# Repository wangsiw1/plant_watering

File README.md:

# Plant watering

A simple 1 main to multiple workers hardware setup to monitor soil moisture and water series of plant pots automatically.

Main device:
- Gateway of the setup, managing the workers, hosting web server for user interactions
- Monitoring water level from water container with capacitive sensor
- Controlling pump for watering

Worker device:
- Monitoring 1 or more soil moisture sensors and reporting to main
- Controlling 1 or more two-position three-way solenoid valves to redirect water to different plant pots

> **Disclaimer**: LLM has been used in this project as part of the learning process. On hardware side, Google Gemini, Claude AI, and OpenAI ChatGPT were used to explain usage of components, knowledge cross check, and parts recommendation. On software side, GitHub Copilot agent in Visual Studio Code was used to generate part of the code based on design document. Human review, revise, and test was conducted every round of generation.

## Design

- MCU:
    Considering the price and wireless requirement, ESP32 C3 was chosen.

- Power: 
    - Since main device will do the heavy duties(Always on, WiFi connection and web server host, pump driving, etc.), a 12V DC input using common DC barrel plug adapter was used to provide continuous power. 
    - Amount of workers can be scaled up and locations varies based on the plant location, while worker can be less power hungry, rechargeable LiPo battery is used.

- Communication:
    - Bluetooth between main and worker for sensor reading reporting and watering command sending. 
    - For easy scalability and setup process, all devices use BLE broadcast to send messages and filter message by MAC address of sendor, no connection is required.

- Function:
    - Users add workers to main by Bluetooth MAC address. Main will probe added workers and learn details upon first status report(worker having 1/8/16 ports available)
    - Users set watering duration, soil moisture threshold, and automatic watering interval for each plant pot, plus the system-wide active time range and data-sync interval.
    - After enabling auto watering, main collects sensor readings, starts pump and commands workers to trigger solenoid valve, then let workers go to deep sleep mode during time interval to save power.
    - Solenoid valve will be triggered one by one, meaning only one pot will be watered at a single time, due to battery current and pump power limitation.

## Hardware

### V1

For the initial idea, because of the nature of similarity between main and worker(1 sensor, 1 peripheral), it was decided to use a single PCB design for both devices with compatibility added to fit different parts on the same board. 

Since a 12V pump was used, a 12V solenoid valve was also chosen. Then all differences are as follow:
- Different sockets for pump(screw terminal) and valve(GH 1.25 socket), lined up next to each other on the PCB, use one of them as needed.
- Different sensor pin numbers(3 pins for soil moisture and 4 pins for water level), since both are XH 2.54, and both have pin 3 as data output, put a single 4 pin footprint, and use different parts.
- Different VIN and GND pin sequences for sensors, use two 0 ohm with solder pads in 2*2 grid to bridge trace to achieve different sequences on different orientations.

Being first version of the project and first personal hardware project, this one has severe design flaws due to lacking of knowledge, hardware understanding, and product reasearch. It was scrapped later.

#### Shared Schematic & PCB

#### Main

#### Worker

### V2

Design of main device is basically V1, but with dimension changed to fit case and worker compatibility removed, as worker is fully redesigned.

For worker, after reviewing the total cost of V1 worker, it was really expensive for users owning dozens of pots of plant. In V2, worker had numbers of monitored plant expand from 1 to 8, and can be expanded to 16 in the future.

To reduce cost and weight, power was cut from 12V to 5V. Battery was moved from large lithium battery pack to flat LiPo with charging & 5V boost converter module. Solenoid valve was also changed to a different 5V version.

There are still several minor issues with this version, not function breaking, but are documented in the schematic and shall be fixed in the next revision.

#### Main

#### Worker

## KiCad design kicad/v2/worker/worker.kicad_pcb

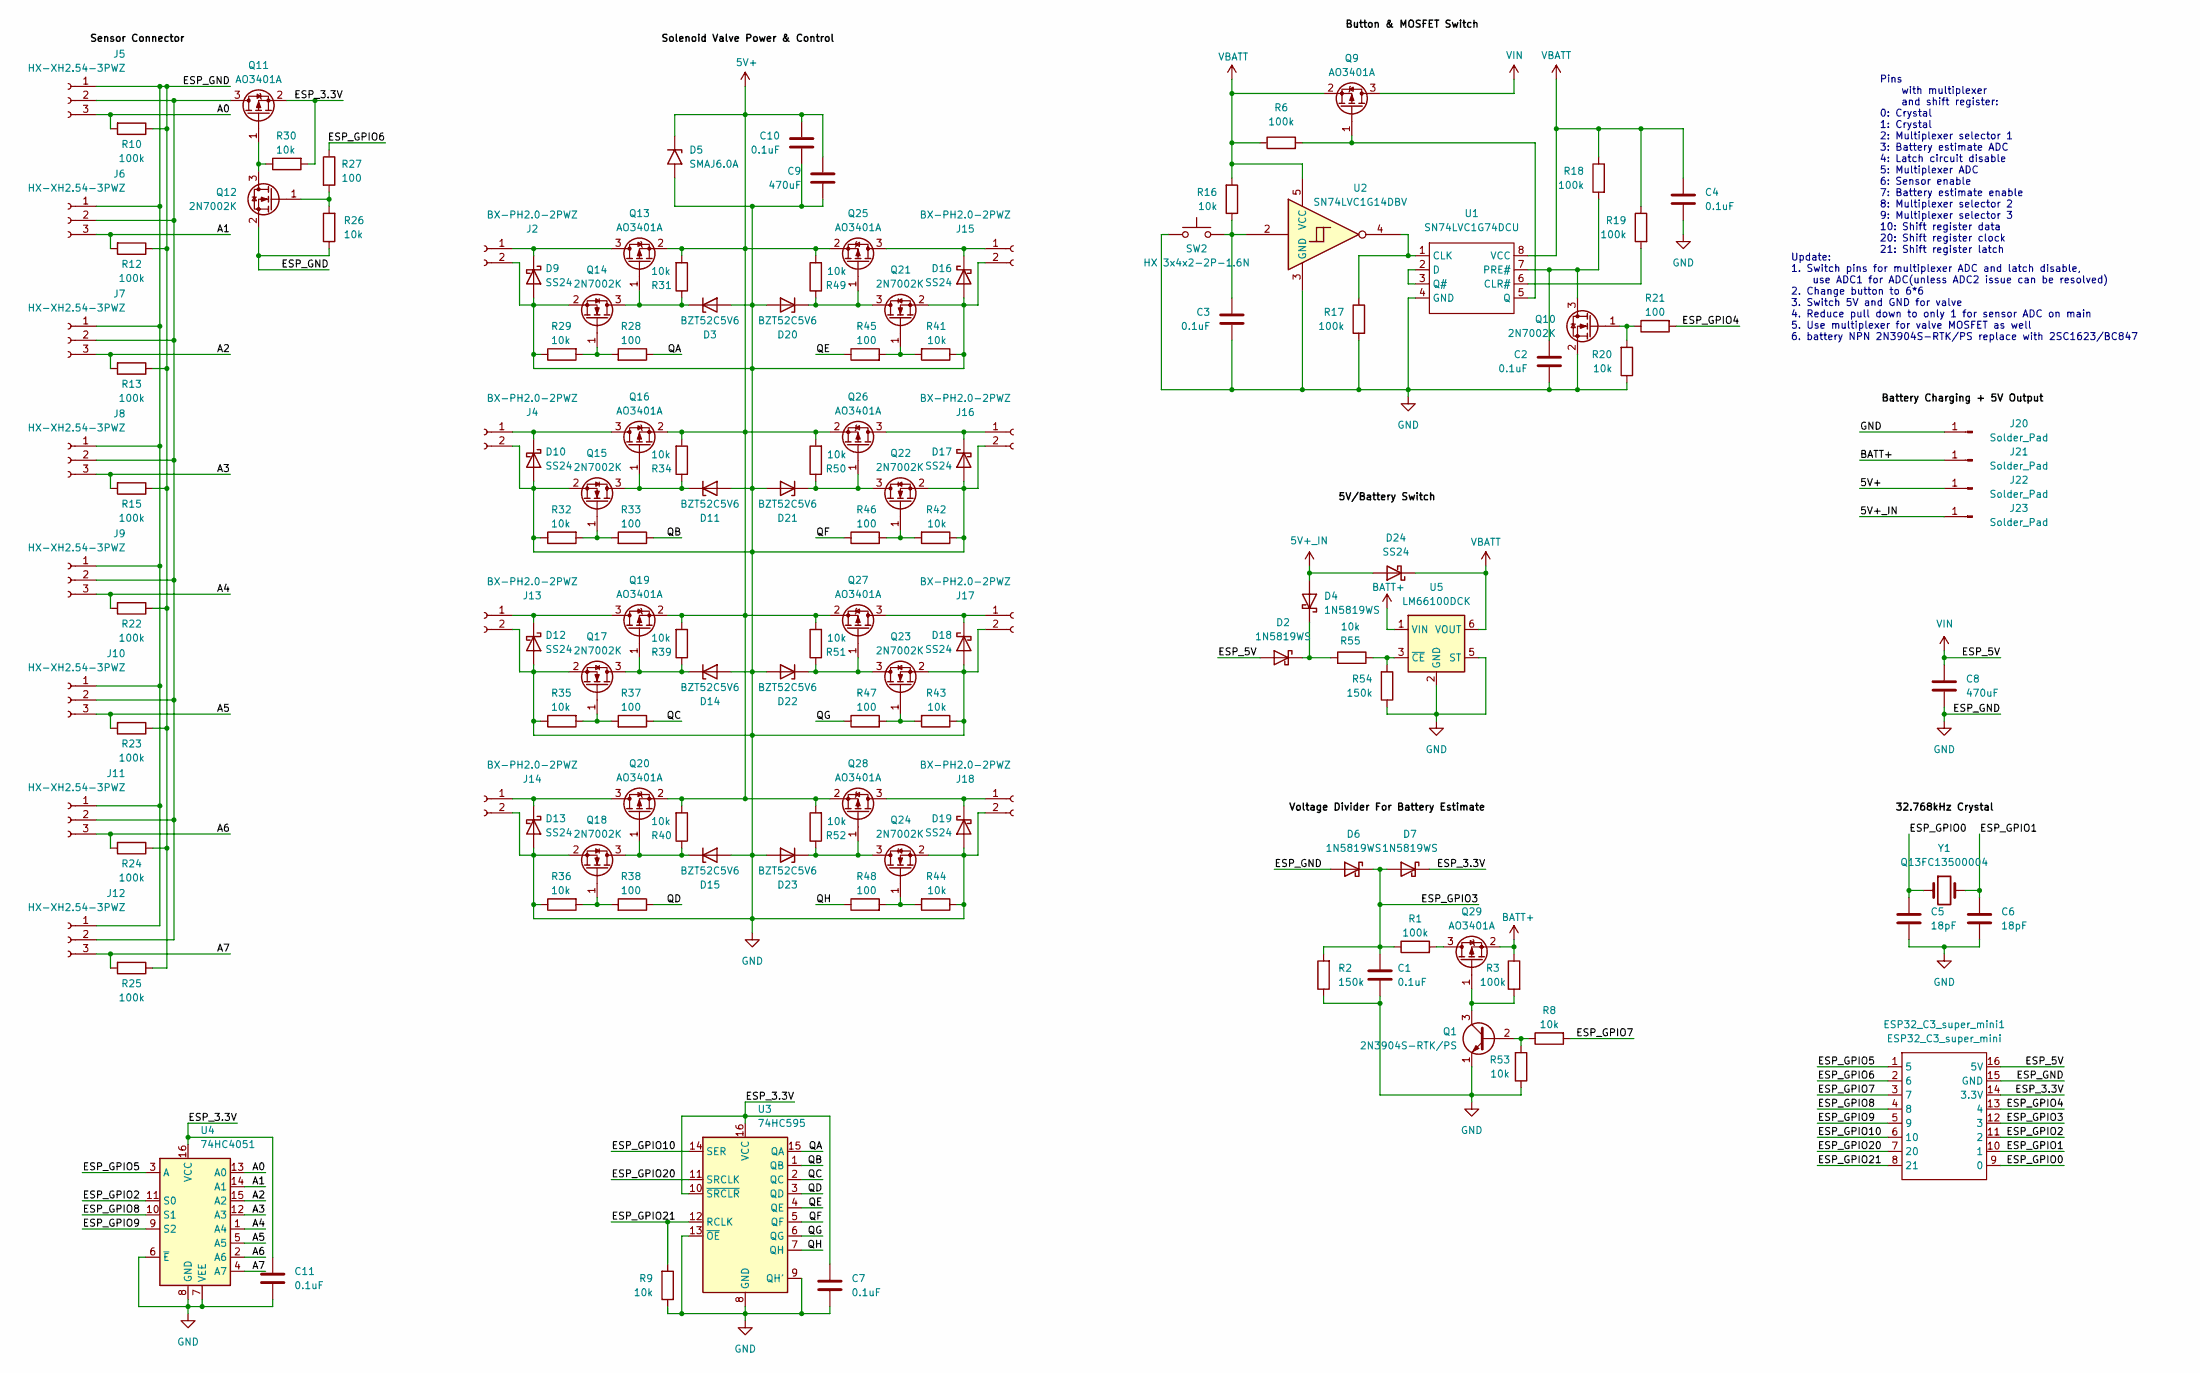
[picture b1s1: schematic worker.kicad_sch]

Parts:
C1, C2, C3, C4, C7, C10, C11: 0.1uF; C_0603_1608Metric
C5, C6: 18pF; C_0603_1608Metric
C8, C9: 470uF; CP_Elec_6.3x7.7
D2, D4, D6, D7: 1N5819WS; D_SOD-323
D3, D11, D14, D15, D20, D21, D22, D23: BZT52C5V6; D_SOD-123
D5: SMAJ6.0A; D_SMA
D9, D10, D12, D13, D16, D17, D18, D19, D24: SS24; D_SMA
ESP32_C3_super_mini1: ESP32_C3_super_mini; 1_ESP32_C3_super_mini-SMD_16P-L22.5-W18.0-P2.54-TL
J2, J4, J13, J14, J15, J16, J17, J18: BX-PH2.0-2PWZ; JST_PH_B2B-PH-K_1x02_P2.00mm_Vertical
J5, J6, J7, J8, J9, J10, J11, J12: HX-XH2.54-3PWZ; JST_XH_B3B-XH-A_1x03_P2.50mm_Vertical
J20, J21, J22, J23: Solder_Pad; SolderWirePad_1x01_SMD_2x4mm
Q1: 2N3904S-RTK/PS; SOT-23
Q9, Q11, Q13, Q16, Q19, Q20, Q25, Q26, Q27, Q28, Q29: AO3401A; SOT-23
Q10, Q12, Q14, Q15, Q17, Q18, Q21, Q22, Q23, Q24: 2N7002K; SOT-23
R1, R3, R6, R10, R12, R13, R15, R17, R18, R19, R22, R23, R24, R25: 100k; R_0603_1608Metric
R2, R54: 150k; R_0603_1608Metric
R8, R9, R16, R20, R26, R29, R30, R31, R32, R34, R35, R36, R39, R40, R41, R42, R43, R44, R49, R50, R51, R52, R53, R55: 10k; R_0603_1608Metric
R21, R27, R28, R33, R37, R38, R45, R46, R47, R48: 100; R_0603_1608Metric
SW2: HX 3x4x2-2P-1.6N; SW_Push_SPST_NO_Alps_SKRK
U1: SN74LVC1G74DCU; VSSOP-8_2.3x2mm_P0.5mm
U2: SN74LVC1G14DBV; SOT-23-5
U3: 74HC595; TSSOP-16_4.4x5mm_P0.65mm
U4: 74HC4051; TSSOP-16_4.4x5mm_P0.65mm
U5: LM66100DCK; SOT-363_SC-70-6
Y1: Q13FC13500004; Crystal_SMD_3215-2Pin_3.2x1.5mm

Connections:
5V+: C9.1, C10.2, D5.1 (A1), J22.1 (Pin_1_1), Q13.2 (S), Q16.2 (S), Q19.2 (S), Q20.2 (S), Q25.2 (S), Q26.2 (S), Q27.2 (S), Q28.2 (S), R31.2, R34.2, R39.2, R40.2, R49.2, R50.2, R51.2, R52.2
5V+_IN: D4.2 (A), D24.2 (A), J23.1 (Pin_1_1)
/A0: J5.3, R10.2, U4.13 (A0)
/A1: J6.3, R12.2, U4.14 (A1)
/A2: J7.3, R13.2, U4.15 (A2)
/A3: J8.3, R15.2, U4.12 (A3)
/A4: J9.3, R22.2, U4.1 (A4)
/A5: J10.3, R23.2, U4.5 (A5)
/A6: J11.3, R24.2, U4.2 (A6)
/A7: J12.3, R25.2, U4.4 (A7)
/ESP_3.3V: C7.2, C11.2, D7.1 (K), ESP32_C3_super_mini1.14 (3.3V), Q11.2 (S), R30.2, U3.10 (~SRCLR), U3.16 (VCC), U4.16 (VCC)
/ESP_GPIO0: C5.1, ESP32_C3_super_mini1.9 (0), Y1.1
/ESP_GPIO1: C6.1, ESP32_C3_super_mini1.10 (1), Y1.2
/ESP_GPIO2: ESP32_C3_super_mini1.11 (2), U4.11 (S0)
/ESP_GPIO3: C1.2, D6.1 (K), D7.2 (A), ESP32_C3_super_mini1.12 (3), R1.1, R2.2
/ESP_GPIO4: ESP32_C3_super_mini1.13 (4), R21.2
/ESP_GPIO5: ESP32_C3_super_mini1.1 (5), U4.3 (A)
/ESP_GPIO6: ESP32_C3_super_mini1.2 (6), R27.1
/ESP_GPIO7: ESP32_C3_super_mini1.3 (7), R8.2
/ESP_GPIO8: ESP32_C3_super_mini1.4 (8), U4.10 (S1)
/ESP_GPIO9: ESP32_C3_super_mini1.5 (9), U4.9 (S2)
/ESP_GPIO10: ESP32_C3_super_mini1.6 (10), U3.14 (SER)
/ESP_GPIO20: ESP32_C3_super_mini1.7 (20), U3.11 (SRCLK)
/ESP_GPIO21: ESP32_C3_super_mini1.8 (21), R9.2, U3.12 (RCLK)
/QA: R28.1, U3.15 (QA)
/QB: R33.1, U3.1 (QB)
/QC: R37.1, U3.2 (QC)
/QD: R38.1, U3.3 (QD)
/QE: R45.1, U3.4 (QE)
/QF: R46.1, U3.5 (QF)
/QG: R47.1, U3.6 (QG)
/QH: R48.1, U3.7 (QH)
BATT+: J21.1 (Pin_1_1), Q29.2 (S), R3.1, U5.1 (VIN)
GND: C1.1, C2.1, C3.1, C4.1, C5.2, C6.2, C7.1, C8.2, C9.2, C10.1, C11.1, D3.2 (A), D5.2 (A2), D6.2 (A), D9.2 (A), D10.2 (A), D11.2 (A), D12.2 (A), D13.2 (A), D14.2 (A), D15.2 (A), D16.2 (A), D17.2 (A), D18.2 (A), D19.2 (A), D20.2 (A), D21.2 (A), D22.2 (A), D23.2 (A), ESP32_C3_super_mini1.15 (GND), J2.2, J4.2, J5.1, J6.1, J7.1, J8.1, J9.1, J10.1, J11.1, J12.1, J13.2, J14.2, J15.2, J16.2, J17.2, J18.2, J20.1 (Pin_1_1), Q1.1 (E), Q10.2 (S), Q12.2 (S), Q14.2 (S), Q15.2 (S), Q17.2 (S), Q18.2 (S), Q21.2 (S), Q22.2 (S), Q23.2 (S), Q24.2 (S), R2.1, R9.1, R10.1, R12.1, R13.1, R15.1, R17.2, R20.1, R22.1, R23.1, R24.1, R25.1, R26.1, R29.1, R32.1, R35.1, R36.1, R41.1, R42.1, R43.1, R44.1, R53.1, R54.1, SW2.1, U1.4 (GND), U2.3 (GND), U3.8 (GND), U3.9 (QH'), U3.13 (~OE), U4.6 (~E), U4.7 (VEE), U4.8 (GND), U5.2 (GND), U5.5 (ST)
unnamed: C3.2, R16.1, SW2.2, U2.2
unnamed: D2.1 (K), D4.1 (K), R55.2
unnamed: D3.1 (K), Q13.1 (G), Q14.3 (D), R31.1
unnamed: D9.1 (K), J2.1, Q13.3 (D)
unnamed: D10.1 (K), J4.1, Q16.3 (D)
unnamed: D11.1 (K), Q15.3 (D), Q16.1 (G), R34.1
unnamed: D12.1 (K), J13.1, Q19.3 (D)
unnamed: D13.1 (K), J14.1, Q20.3 (D)
unnamed: D14.1 (K), Q17.3 (D), Q19.1 (G), R39.1
unnamed: D15.1 (K), Q18.3 (D), Q20.1 (G), R40.1
unnamed: D16.1 (K), J15.1, Q25.3 (D)
unnamed: D17.1 (K), J16.1, Q26.3 (D)
unnamed: D18.1 (K), J17.1, Q27.3 (D)
unnamed: D19.1 (K), J18.1, Q28.3 (D)
unnamed: D20.1 (K), Q21.3 (D), Q25.1 (G), R49.1
unnamed: D21.1 (K), Q22.3 (D), Q26.1 (G), R50.1
unnamed: D22.1 (K), Q23.3 (D), Q27.1 (G), R51.1
unnamed: D23.1 (K), Q24.3 (D), Q28.1 (G), R52.1
unnamed: J5.2, J6.2, J7.2, J8.2, J9.2, J10.2, J11.2, J12.2, Q11.3 (D)
unnamed: Q1.2 (B), R8.1, R53.2
unnamed: Q1.3 (C), Q29.1 (G), R3.2
unnamed: Q9.1 (G), R6.2, U1.5 (Q)
unnamed: C2.2, Q10.3 (D), R18.2, U1.7 (PRE#)
unnamed: Q10.1 (G), R20.2, R21.1
unnamed: Q11.1 (G), Q12.3 (D), R30.1
unnamed: Q12.1 (G), R26.2, R27.2
unnamed: Q14.1 (G), R28.2, R29.2
unnamed: Q15.1 (G), R32.2, R33.2
unnamed: Q17.1 (G), R35.2, R37.2
unnamed: Q18.1 (G), R36.2, R38.2
unnamed: Q21.1 (G), R41.2, R45.2
unnamed: Q22.1 (G), R42.2, R46.2
unnamed: Q23.1 (G), R43.2, R47.2
unnamed: Q24.1 (G), R44.2, R48.2
unnamed: Q29.3 (D), R1.2
unnamed: R17.1, U1.1 (CLK), U2.4
unnamed: R19.2, U1.6 (CLR#)
unnamed: U1.2 (D), U1.3 (Q#)
unnamed: R54.2, R55.1, U5.3 (~CE)
VBATT: C4.2, D24.1 (K), Q9.2 (S), R6.1, R16.2, R18.1, R19.1, U1.8 (VCC), U2.5 (VCC), U5.6 (VOUT)
VIN: C8.1, D2.2 (A), ESP32_C3_super_mini1.16 (5V), Q9.3 (D)

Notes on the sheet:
Update: 1. Switch pins for multiplexer ADC and latch disable, use ADC1 for ADC(unless ADC2 issue can be resolved) 2. Change button to 6*6 3. Switch 5V and GND for valve 4. Reduce pull down to only 1 for sensor ADC on main 5. Use multiplexer for valve MOSFET as well 6. battery NPN 2N3904S-RTK/PS rep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
Pins with multiplexer and shift register: 0: Crystal 1: Crystal 2: Multiplexer selector 1 3: Battery estimate ADC 4: Latch circuit disable 5: Multiplexer ADC 6: Sensor enable 7: Battery estimate enable 8: Multiplexer selector 2 9: Multiplexer selector 3 10: Shift register data 20: Shift register cl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

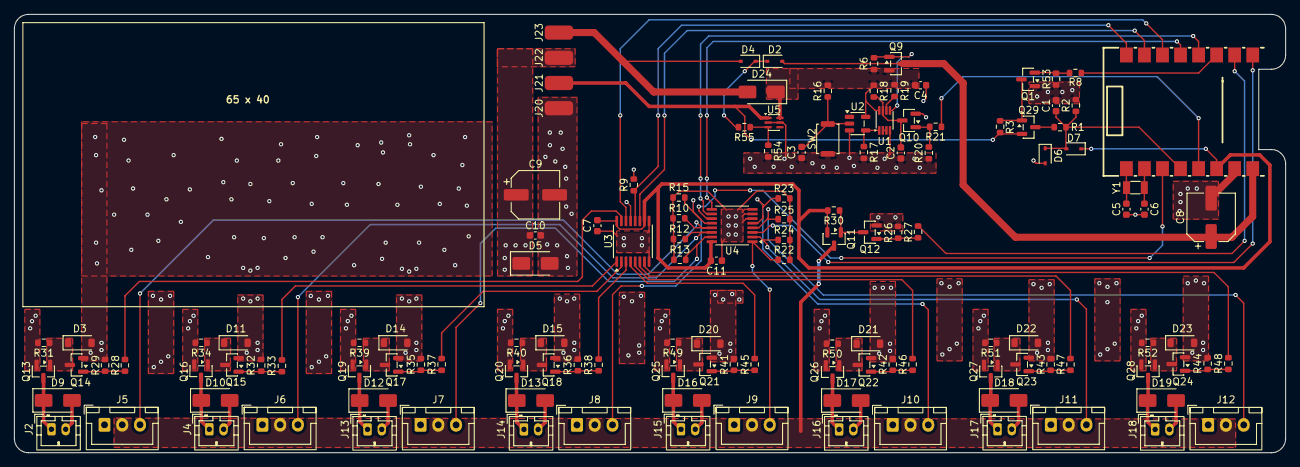
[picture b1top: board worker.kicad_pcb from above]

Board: 2 copper layers, 178.9 x 61.7 mm, 133 parts (0 on the bottom side), 75 nets.

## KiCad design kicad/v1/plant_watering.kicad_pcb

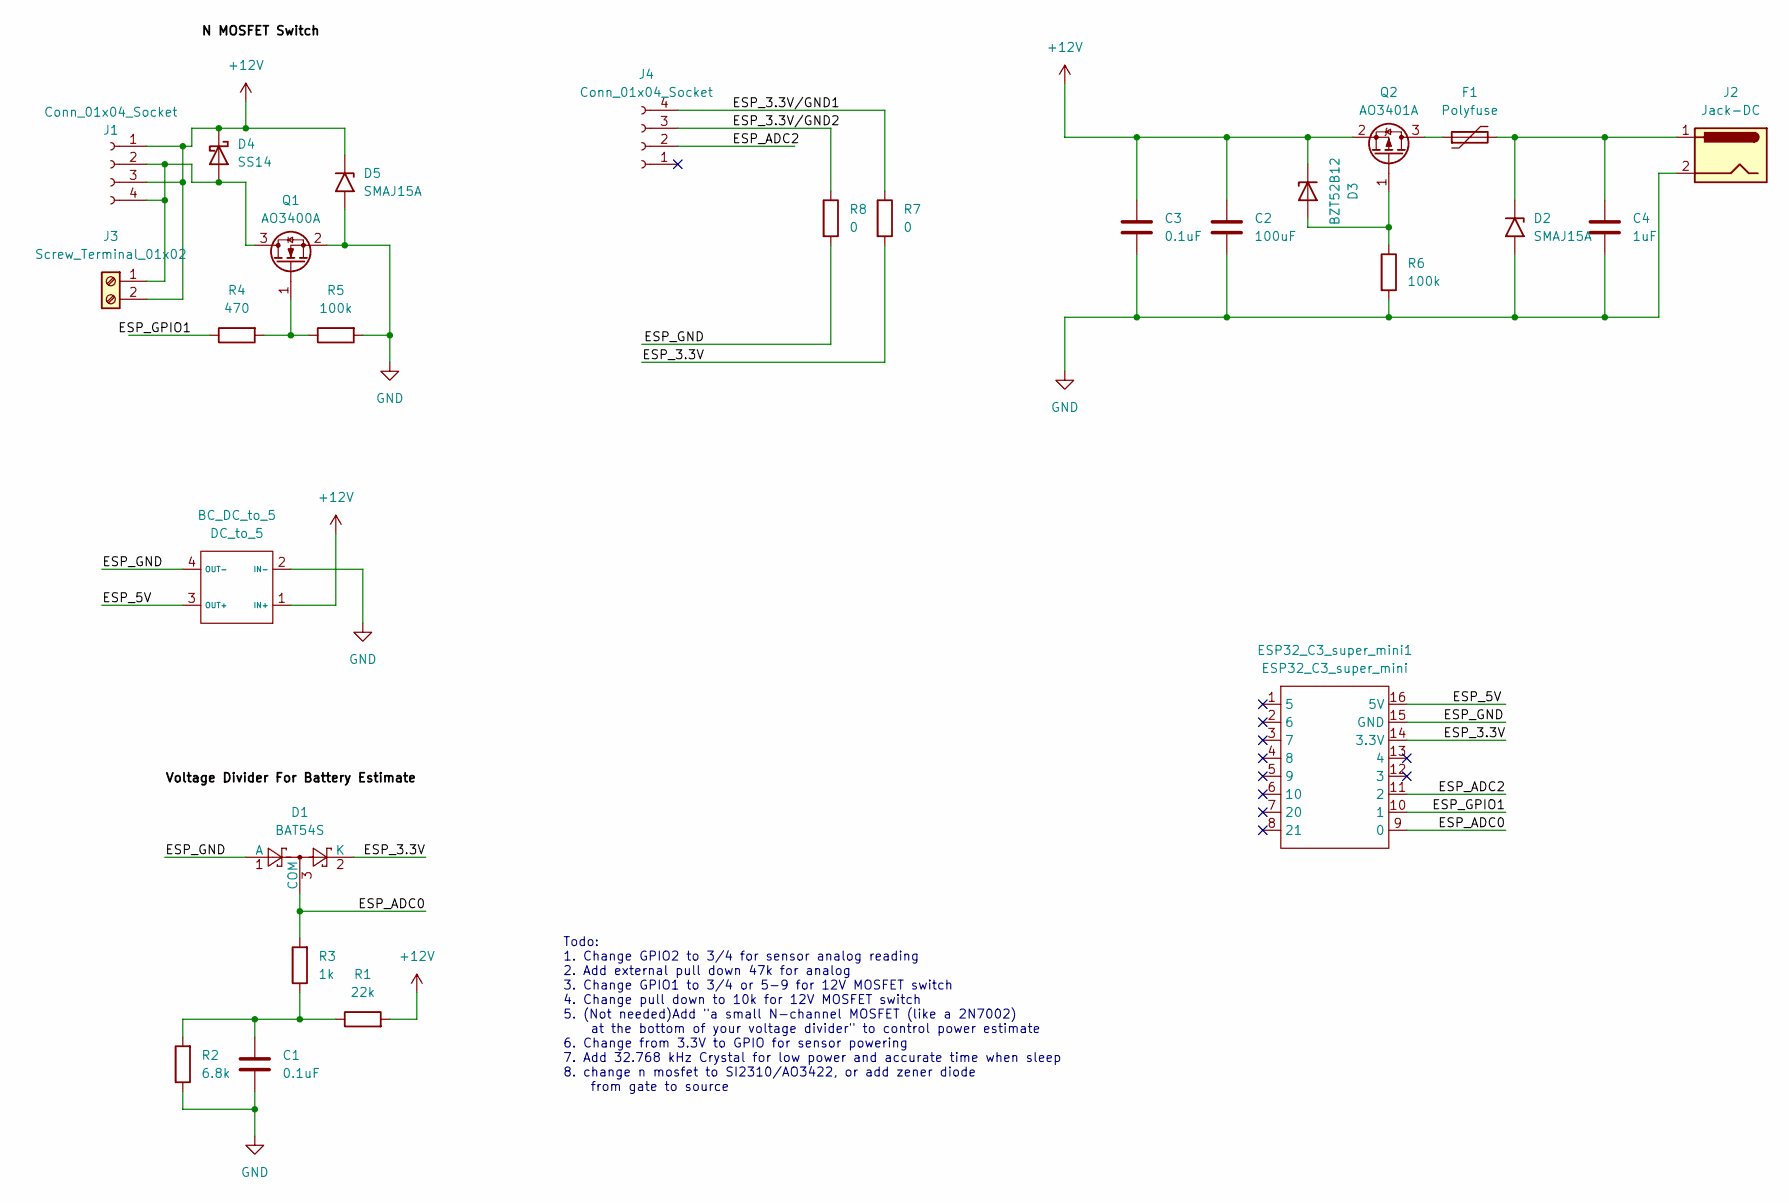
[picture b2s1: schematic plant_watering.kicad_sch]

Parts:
BC_DC_to_5: DC_to_5; COMM-SMD_12VTO5V
C1, C3: 0.1uF; C_0603_1608Metric
C2: 100uF; CP_Elec_6.3x5.4
C4: 1uF; C_0603_1608Metric
D1: BAT54S; SOT-23
D2, D5: SMAJ15A; D_SMA
D3: BZT52B12; D_SOD-123
D4: SS14; D_SMA
ESP32_C3_super_mini1: ESP32_C3_super_mini; 1_ESP32_C3_super_mini-SMD_16P-L22.5-W18.0-P2.54-TL
F1: Polyfuse; Fuse_1812_4532Metric
J1: Conn_01x04_Socket; CONN-SMD_2P-P1.25_XYECONN_XY-GH1.25-2A61
J2: Jack-DC; DC-IN-TH_DC-470-2.1GP
J3: Screw_Terminal_01x02; CONN-TH_WJ126V-5.0-2P
J4: Conn_01x04_Socket; CONN-TH_4P-P2.50-XH2.54-4P
Q1: AO3400A; SOT-23
Q2: AO3401A; SOT-23
R1: 22k; R_0603_1608Metric
R2: 6.8k; R_0603_1608Metric
R3: 1k; R_0603_1608Metric
R4: 470; R_0603_1608Metric
R5, R6: 100k; R_0603_1608Metric
R7, R8: 0; R_0603_1608Metric_Pad0.98x0.95mm_HandSolder

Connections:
+12V: BC_DC_to_5.1 (IN+), C2.1, C3.1, D3.1 (K), D4.1 (K), D5.1 (A1), J1.1, J1.3, J3.2, Q2.2 (S), R1.2
/ESP_3.3V: D1.2 (K), ESP32_C3_super_mini1.14 (3.3V), R7.2
/ESP_3.3V/GND1: J4.4, R7.1
/ESP_3.3V/GND2: J4.3, R8.1
/ESP_5V: BC_DC_to_5.3 (OUT+), ESP32_C3_super_mini1.16 (5V)
/ESP_ADC0: D1.3 (COM), ESP32_C3_super_mini1.9 (0), R3.2
/ESP_ADC2: ESP32_C3_super_mini1.11 (2), J4.2
/ESP_GND: BC_DC_to_5.4 (OUT-), D1.1 (A), ESP32_C3_super_mini1.15 (GND), R8.2
/ESP_GPIO1: ESP32_C3_super_mini1.10 (1), R4.1
GND: BC_DC_to_5.2 (IN-), C1.1, C2.2, C3.2, C4.2, D2.2 (A2), D5.2 (A2), J2.2, Q1.2 (S), R2.1, R5.2, R6.2
unnamed: C1.2, R1.1, R2.2, R3.1
unnamed: C4.1, D2.1 (A1), F1.2, J2.1
unnamed: D3.2 (A), Q2.1 (G), R6.1
unnamed: D4.2 (A), J1.2, J1.4, J3.1, Q1.3 (D)
unnamed: Q1.1 (G), R4.2, R5.1
unnamed: F1.1, Q2.3 (D)

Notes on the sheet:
Todo: 1. Change GPIO2 to 3/4 for sensor analog reading 2. Add external pull down 47k for analog 3. Change GPIO1 to 3/4 or 5-9 for 12V MOSFET switch 4. Change pull down to 10k for 12V MOSFET switch 5. (Not needed)Add "a small N-channel MOSFET (like a 2N7002) at the bottom of your voltage divider" to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

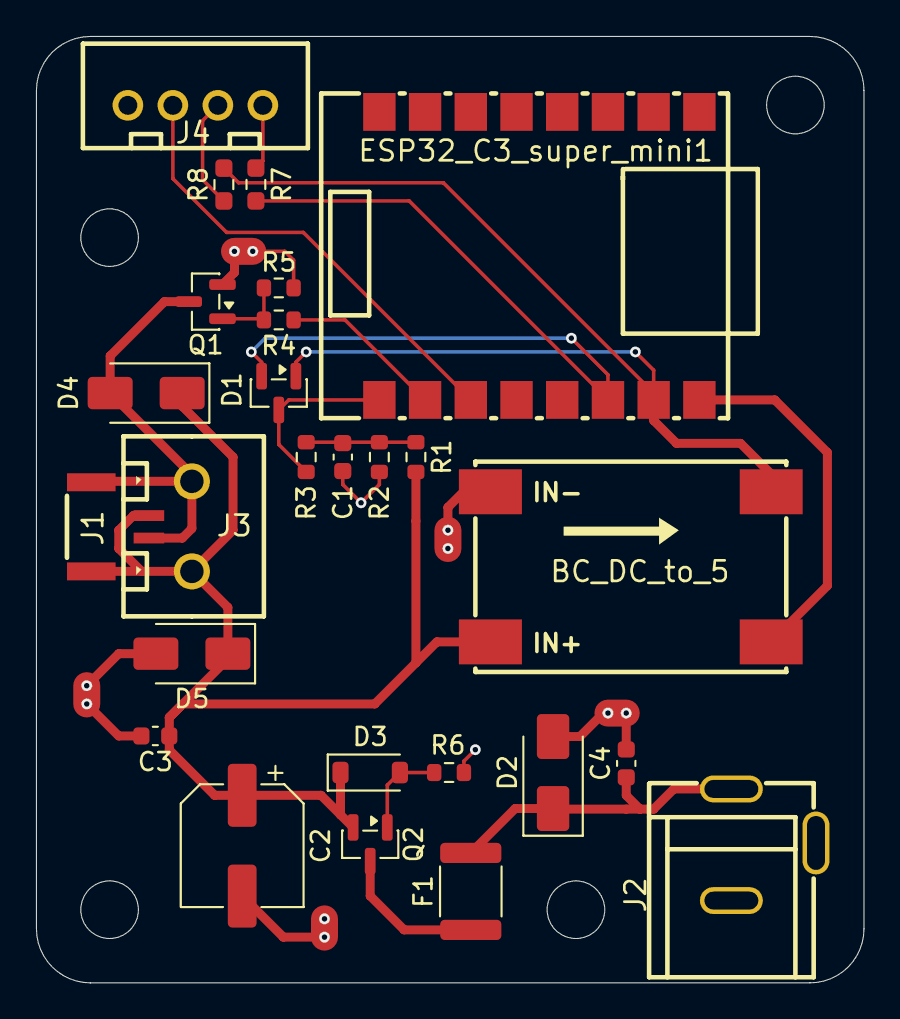
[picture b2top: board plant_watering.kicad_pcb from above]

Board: 2 copper layers, 46.0 x 52.6 mm, 26 parts (0 on the bottom side), 16 nets.

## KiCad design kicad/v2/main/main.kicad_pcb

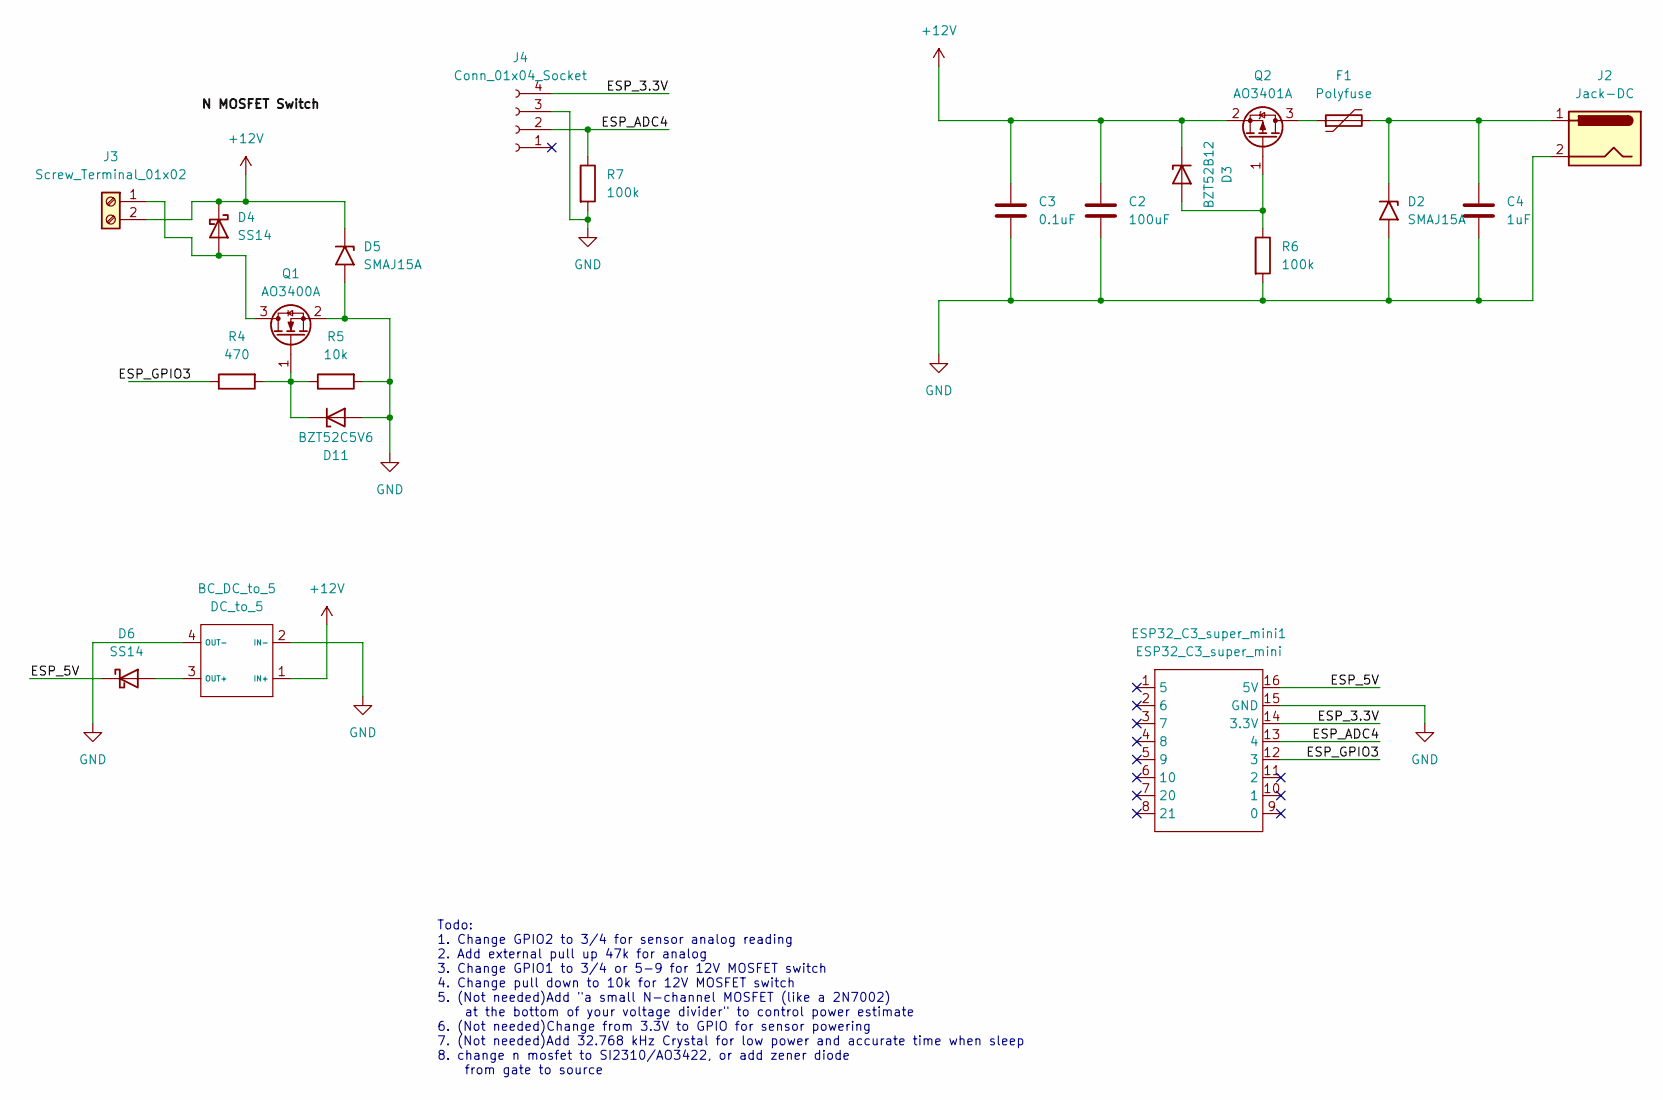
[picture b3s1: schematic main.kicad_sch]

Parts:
BC_DC_to_5: DC_to_5; COMM-SMD_12VTO5V
C2: 100uF; CP_Elec_6.3x5.4
C3: 0.1uF; C_0603_1608Metric
C4: 1uF; C_0603_1608Metric
D2, D5: SMAJ15A; D_SMA
D3: BZT52B12; D_SOD-123
D4, D6: SS14; D_SMA
D11: BZT52C5V6; D_SOD-123
ESP32_C3_super_mini1: ESP32_C3_super_mini; 1_ESP32_C3_super_mini-SMD_16P-L22.5-W18.0-P2.54-TL
F1: Polyfuse; Fuse_1812_4532Metric
J2: Jack-DC; DC-IN-TH_DC-470-2.1GP
J3: Screw_Terminal_01x02; CONN-TH_WJ126V-5.0-2P
J4: Conn_01x04_Socket; CONN-TH_4P-P2.50-XH2.54-4P
Q1: AO3400A; SOT-23
Q2: AO3401A; SOT-23
R4: 470; R_0603_1608Metric
R5: 10k; R_0603_1608Metric
R6, R7: 100k; R_0603_1608Metric

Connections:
+12V: BC_DC_to_5.1 (IN+), C2.1, C3.1, D3.1 (K), D4.1 (K), D5.1 (A1), J3.2, Q2.2 (S)
/ESP_3.3V: ESP32_C3_super_mini1.14 (3.3V), J4.4
/ESP_5V: D6.1 (K), ESP32_C3_super_mini1.16 (5V)
/ESP_ADC4: ESP32_C3_super_mini1.13 (4), J4.2, R7.1
/ESP_GPIO3: ESP32_C3_super_mini1.12 (3), R4.1
GND: BC_DC_to_5.2 (IN-), BC_DC_to_5.4 (OUT-), C2.2, C3.2, C4.2, D2.2 (A2), D5.2 (A2), D11.2 (A), ESP32_C3_super_mini1.15 (GND), J2.2, J4.3, Q1.2 (S), R5.2, R6.2, R7.2
unnamed: BC_DC_to_5.3 (OUT+), D6.2 (A)
unnamed: C4.1, D2.1 (A1), F1.2, J2.1
unnamed: D3.2 (A), Q2.1 (G), R6.1
unnamed: D4.2 (A), J3.1, Q1.3 (D)
unnamed: D11.1 (K), Q1.1 (G), R4.2, R5.1
unnamed: F1.1, Q2.3 (D)

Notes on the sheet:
Todo: 1. Change GPIO2 to 3/4 for sensor analog reading 2. Add external pull up 47k for analog 3. Change GPIO1 to 3/4 or 5-9 for 12V MOSFET switch 4. Change pull down to 10k for 12V MOSFET switch 5. (Not needed)Add "a small N-channel MOSFET (like a 2N7002) at the bottom of your voltage divider" to c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

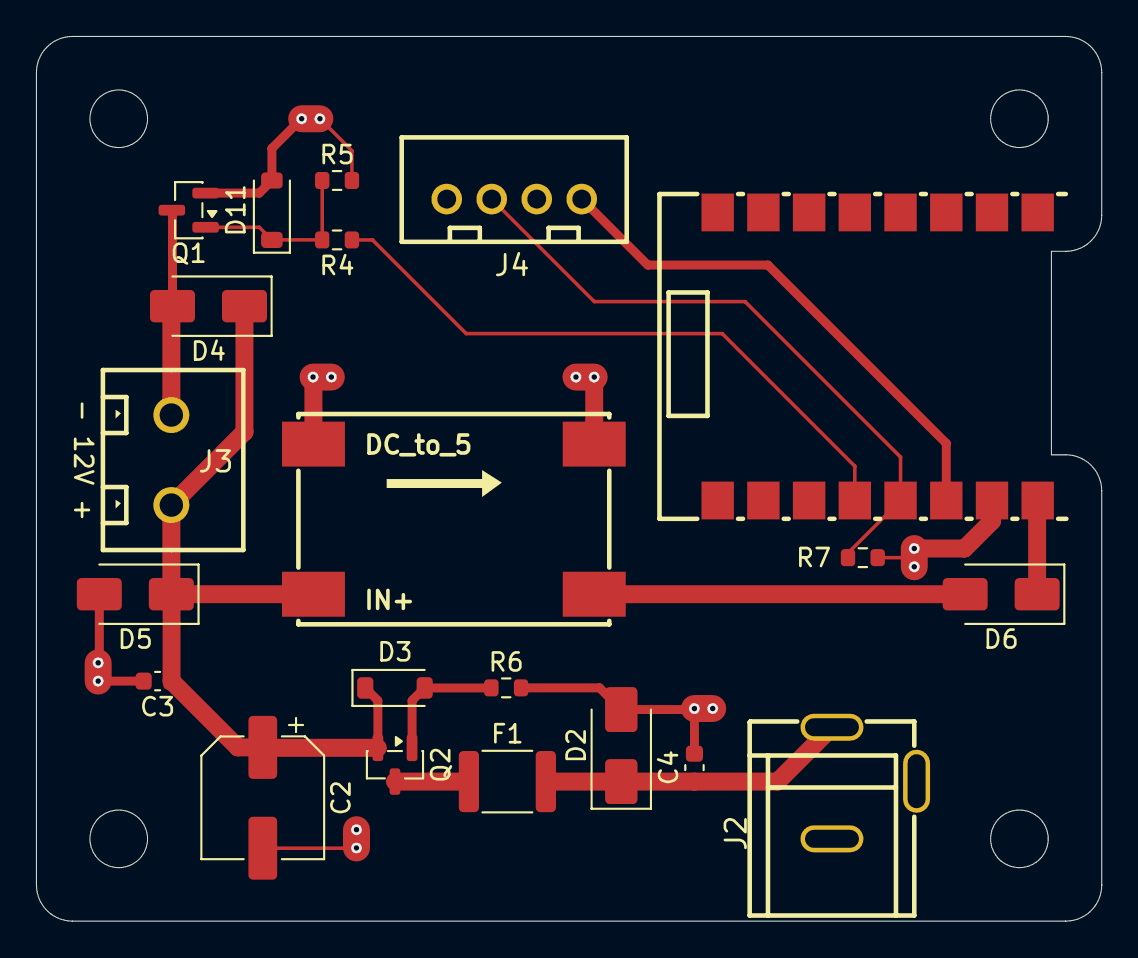
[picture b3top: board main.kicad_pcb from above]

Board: 2 copper layers, 59.2 x 49.1 mm, 21 parts (0 on the bottom side), 12 nets.

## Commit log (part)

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2026-03-06 init commit
2026-03-13 file update
2026-03-13 update worker bluetooth
2026-03-13 more worker bluetooth update
2026-03-13 update watering logic
2026-03-14 add worker files
2026-04-06 v0.1 large changes
2026-05-26 v0.2 large changes, overhaul to support new version of hardware and features
2026-05-26 add kicad and readme
2026-05-26 add images
2026-05-28 update worker battery estimate logic
2026-06-20 version 0.5, mass updates
